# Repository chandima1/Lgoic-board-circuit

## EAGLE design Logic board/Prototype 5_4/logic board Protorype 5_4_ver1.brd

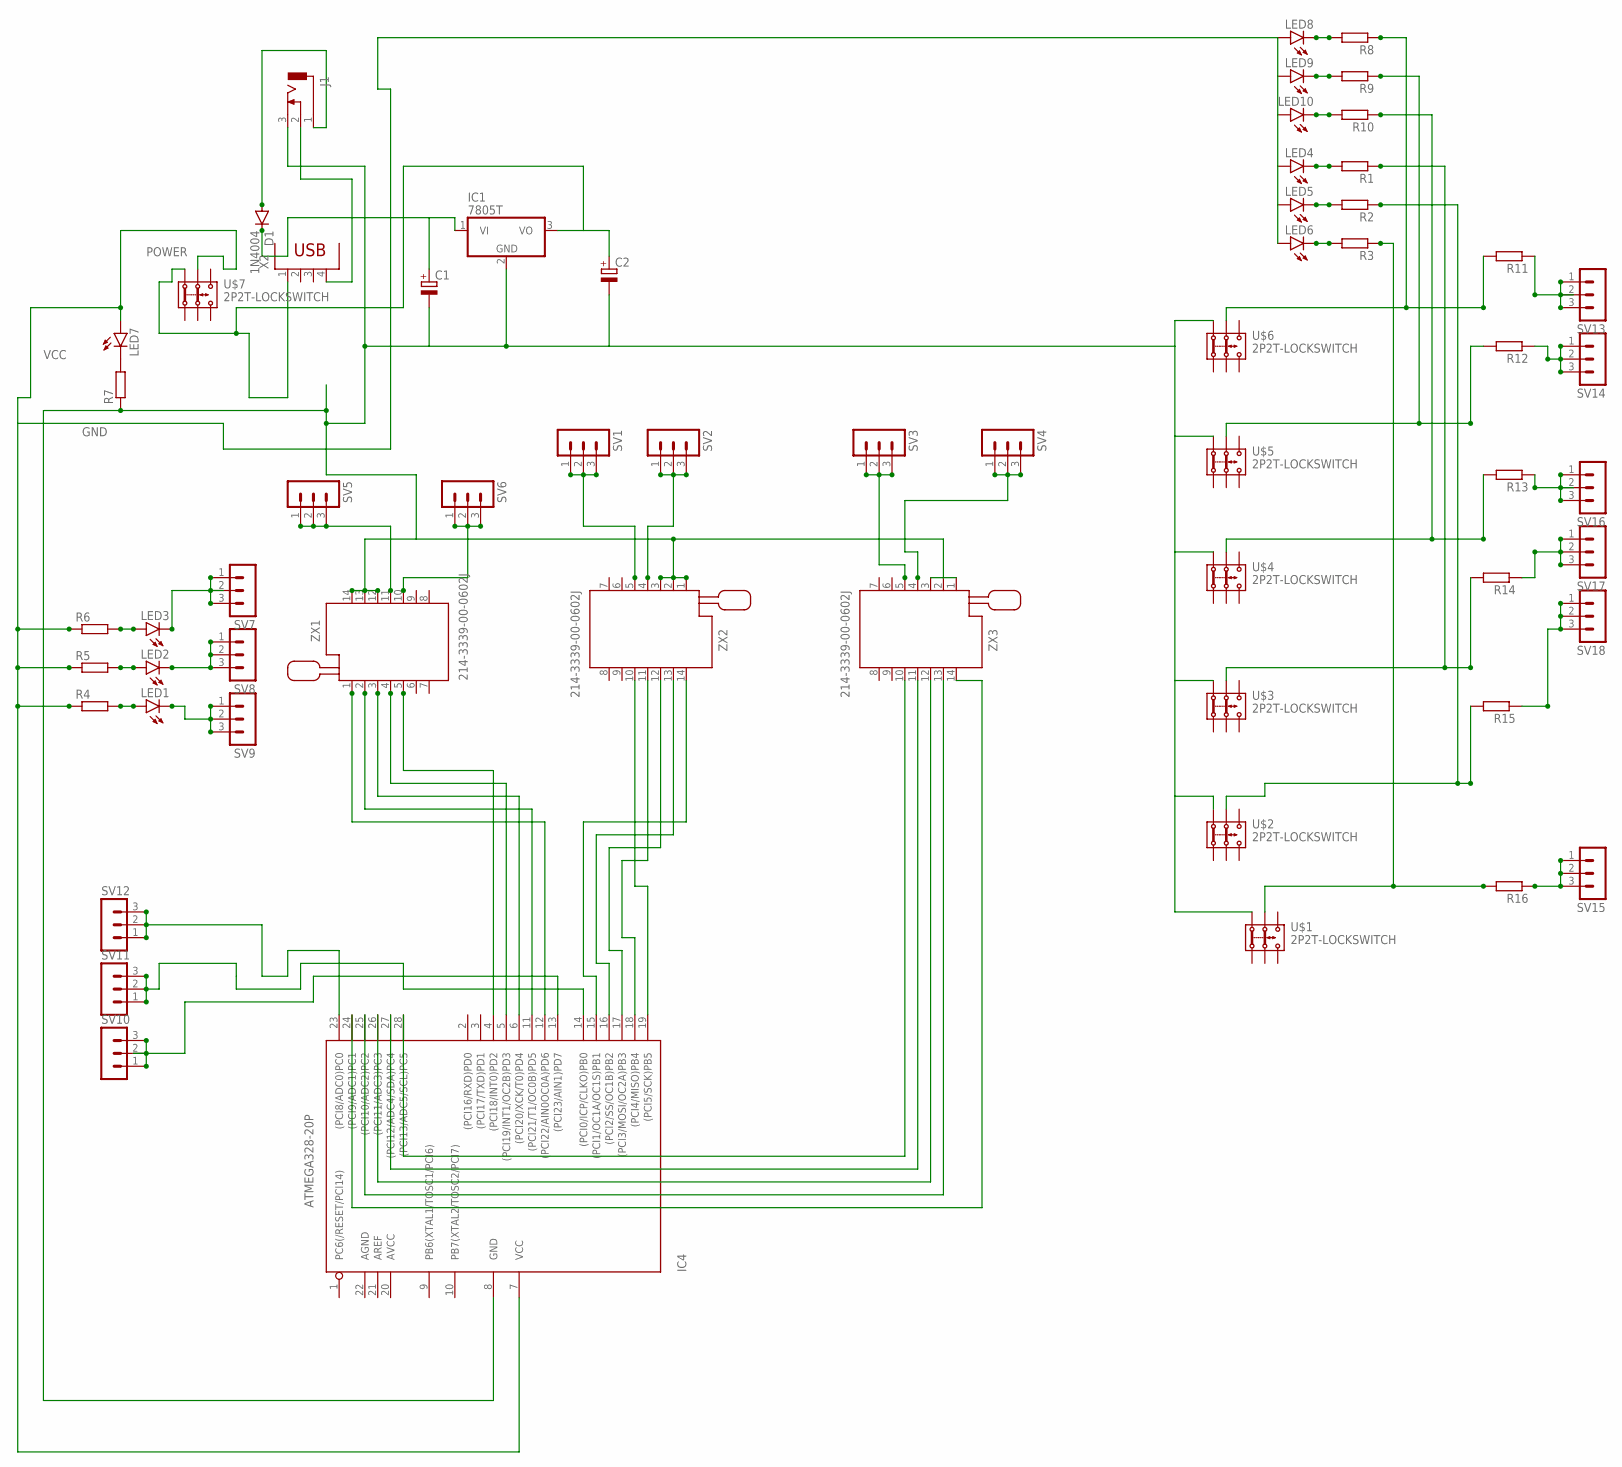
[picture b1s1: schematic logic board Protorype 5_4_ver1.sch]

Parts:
C1, C2: CPOL-EUE2.5-6; E2,5-6
D1: 1N4004; DO41-10
IC1: 7805T; TO220H
IC4: ATMEGA328-20P; DIL28-3
J1: DCJ0303
LED1, LED2, LED3, LED4, LED5, LED6, LED7, LED8, LED9, LED10: LED5MM
R1, R2, R3, R4, R5, R6, R7, R8, R9, R10, R11, R12, R13, R14, R15, R16: R-EU_0207/10; 0207/10
SV1, SV2, SV3, SV4, SV5, SV6, SV7, SV8, SV9, SV10, SV11, SV12, SV13, SV14, SV15, SV16, SV17, SV18: MA03-1
U$1, U$2, U$3, U$4, U$5, U$6, U$7: 2P2T-LOCKSWITCH
X2: PN61729
ZX1, ZX2, ZX3: 214-3339-00-0602J

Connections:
GND: C1.-, C2.-, IC1.2 (GND), IC4.8 (GND), J1.3, R7.1, U$1.1.1, U$2.1.1, U$3.1.1, U$4.1.1, U$5.1.1, U$6.1.1, ZX1.12, ZX1.13, ZX1.14, ZX2.1, ZX2.2, ZX2.3, ZX3.1, ZX3.2, ZX3.3
unnamed: IC4.13 ((PCI23/AIN1)PD7), SV10.1, SV10.2, SV10.3
unnamed: IC4.5 ((PCI19/INT1/OC2B)PD3), ZX1.4
unnamed: LED5.K (C), R2.2
unnamed: IC4.15 ((PCI1/OC1A/OC1S)PB1), ZX2.14
unnamed: IC4.16 ((PCI2/SS/OC1B)PB2), ZX2.13
unnamed: IC4.17 ((PCI3/MOSI/OC2A)PB3), ZX2.12
unnamed: IC4.28 ((PCI13/ADC5/SCL)PC5), ZX3.10
unnamed: IC4.24 ((PCI9/ADC1)PC1), ZX3.14
unnamed: IC4.18 ((PCI4/MISO)PB4), ZX2.11
unnamed: IC4.25 ((PCI10/ADC2)PC2), ZX3.13
unnamed: IC4.19 ((PCI5/SCK)PB5), ZX2.10
unnamed: IC4.23 ((PCI8/ADC0)PC0), SV12.1, SV12.2, SV12.3
unnamed: LED6.K (C), R3.2
unnamed: SV5.1, SV5.2, SV5.3, ZX1.11
unnamed: IC4.27 ((PCI12/ADC4/SDA)PC4), ZX3.11
unnamed: IC4.6 ((PCI20/XCK/T0)PD4), ZX1.3
unnamed: LED2.K (C), SV8.1, SV8.2, SV8.3
unnamed: LED3.A, R6.2
unnamed: LED2.A, R5.2
unnamed: SV6.1, SV6.2, SV6.3, ZX1.10
unnamed: LED3.K (C), SV7.1, SV7.2, SV7.3
unnamed: LED1.A, R4.2
unnamed: IC4.11 ((PCI21/T1/OC0B)PD5), ZX1.2
unnamed: IC4.14 ((PCI0/ICP/CLKO)PB0), SV11.1, SV11.2, SV11.3
unnamed: IC4.4 ((PCI18/INT0)PD2), ZX1.5
unnamed: SV1.1, SV1.2, SV1.3, ZX2.5
unnamed: SV4.1, SV4.2, SV4.3, ZX3.4
unnamed: LED1.K (C), SV9.1, SV9.2, SV9.3
unnamed: SV3.1, SV3.2, SV3.3, ZX3.5
unnamed: SV2.1, SV2.2, SV2.3, ZX2.4
unnamed: IC4.26 ((PCI11/ADC3)PC3), ZX3.12
unnamed: LED7.K (C), R7.2
unnamed: LED4.K (C), R1.2
unnamed: R8.1, R11.2, U$6.2.1
unnamed: IC4.12 ((PCI22/AIN0OC0A)PD6), ZX1.1
unnamed: R9.1, R12.2, U$5.2.1
unnamed: R3.1, R16.2, U$1.2.1
unnamed: LED9.K (C), R9.2
unnamed: LED10.K (C), R10.2
unnamed: LED8.K (C), R8.2
unnamed: R10.1, R13.2, U$4.2.1
unnamed: R2.1, R15.2, U$2.2.1
unnamed: R11.1, SV13.1, SV13.2, SV13.3
unnamed: R1.1, R14.2, U$3.2.1
unnamed: R12.1, SV14.1, SV14.2, SV14.3
unnamed: R13.1, SV16.1, SV16.2, SV16.3
unnamed: R14.1, SV17.1, SV17.2, SV17.3
unnamed: R15.1, SV18.1, SV18.2, SV18.3
unnamed: R16.1, SV15.1, SV15.2, SV15.3
unnamed: J1.2, X2.4
unnamed: D1.A, J1.1
unnamed: C1.+, D1.C, IC1.1 (VI)
POWER: C2.+, IC1.3 (VO), U$7.1.1, X2.1
VCC: IC4.7 (VCC), LED4.A, LED5.A, LED6.A, LED7.A, LED8.A, LED9.A, LED10.A, R4.1, R5.1, R6.1, U$7.2.1

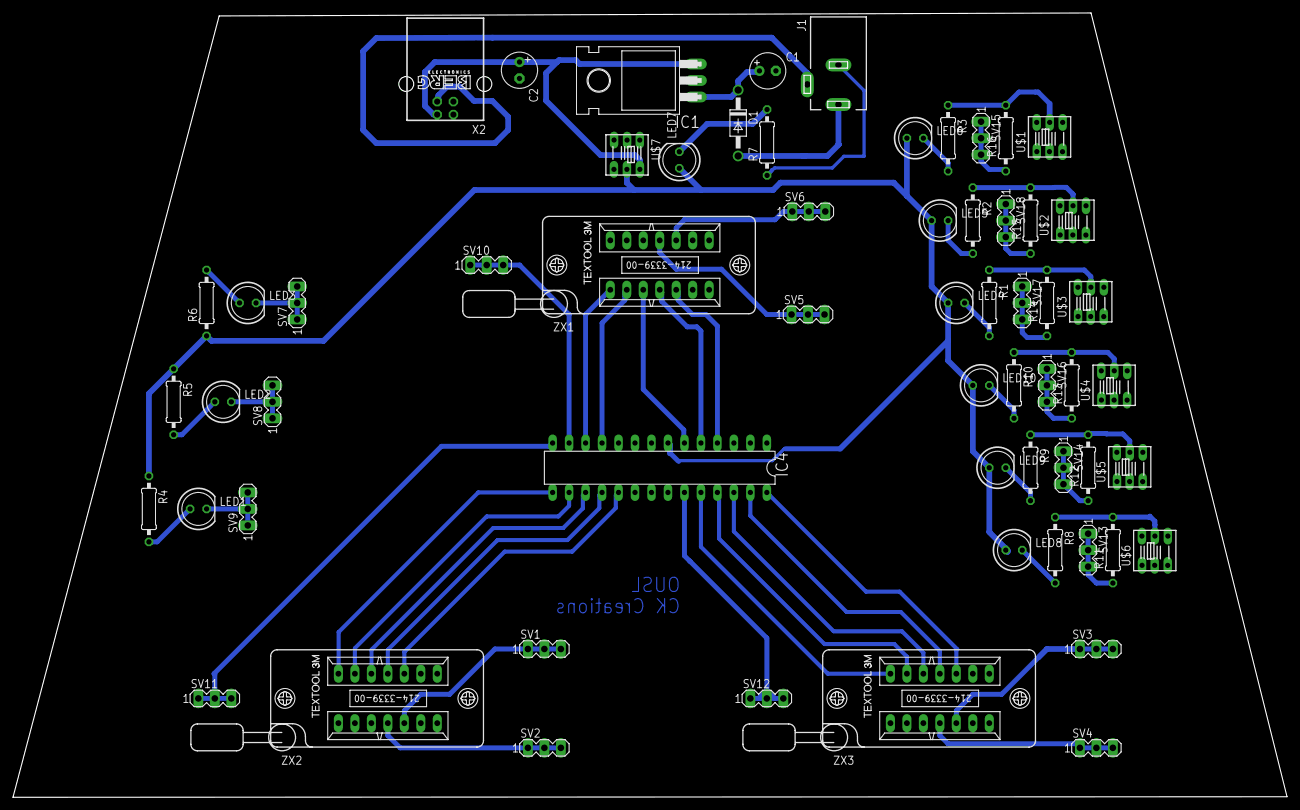
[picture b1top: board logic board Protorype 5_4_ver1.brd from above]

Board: 2 copper layers, 196.4 x 120.9 mm, 61 parts (0 on the bottom side), 55 nets.

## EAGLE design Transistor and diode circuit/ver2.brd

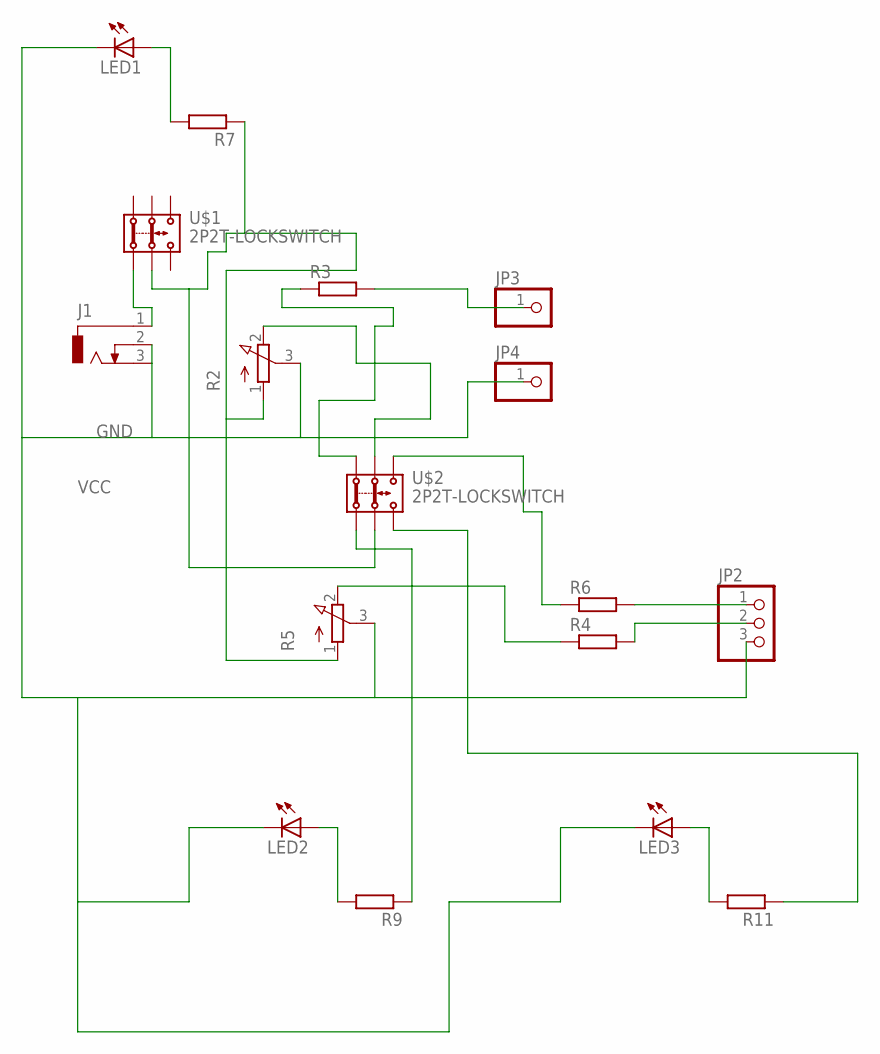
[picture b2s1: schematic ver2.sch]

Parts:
J1: DCJ0303
JP2: PINHD-1X3; 1X03
JP3, JP4: PINHD-1X11X01_CHANDIMA; 1X01_CHANDIMA
LED1, LED2, LED3: LEDLED5MM-CHANDIMA; LED5MM-CHANDIMA
R2, R5: 3RP/1610N3RP_CHANDIMA; 3RP/1610N_CHANDIMA
R3, R4, R6, R7, R9, R11: R-EU_0207/10_CHANDIMA; 0207/10_CHANDIMA
U$1, U$2: 2P2T-LOCKSWITCH

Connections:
GND: J1.2, J1.3, JP2.3, JP4.1, LED1.K (C), LED2.K (C), LED3.K (C), R2.3 (S), R5.3 (S)
unnamed: R2.2 (E), U$2.2.1
unnamed: LED1.A, R7.2
unnamed: R6.1, U$2.3.1
unnamed: J1.1, U$1.1.2
unnamed: JP3.1, R3.2
unnamed: LED3.A, R11.2
unnamed: JP2.1, R6.2
unnamed: R3.1, U$2.1.1
unnamed: JP2.2, R4.2
unnamed: R4.1, R5.2 (E)
unnamed: R9.1, U$2.1.2
unnamed: LED2.A, R9.2
unnamed: R11.1, U$2.3.2
VCC: R2.1 (A), R5.1 (A), R7.1, U$1.2.2, U$2.2.2

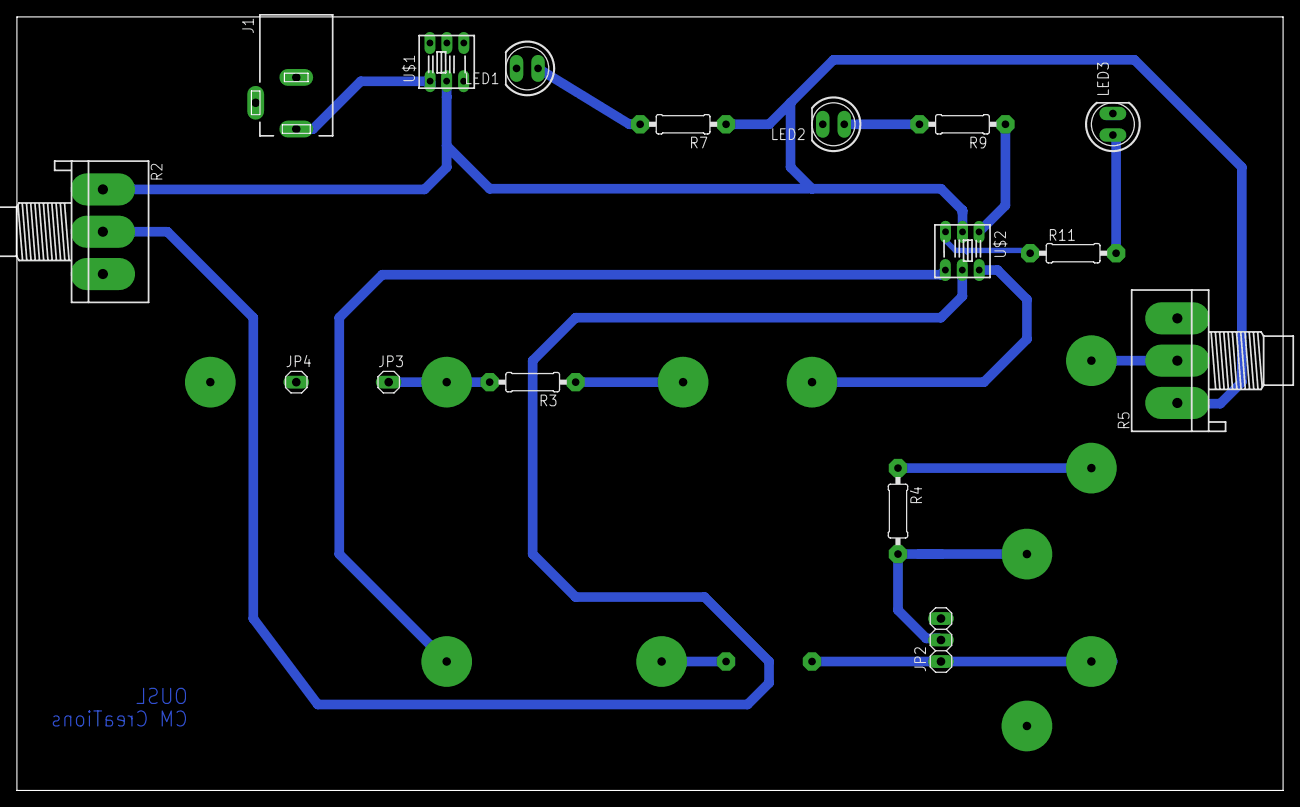
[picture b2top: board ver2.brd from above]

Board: 2 copper layers, 149.7 x 91.4 mm, 17 parts (1 on the bottom side), 15 nets.
